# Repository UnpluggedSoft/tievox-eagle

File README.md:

# tievox-eagle
Eagle drawings for TIEVox.

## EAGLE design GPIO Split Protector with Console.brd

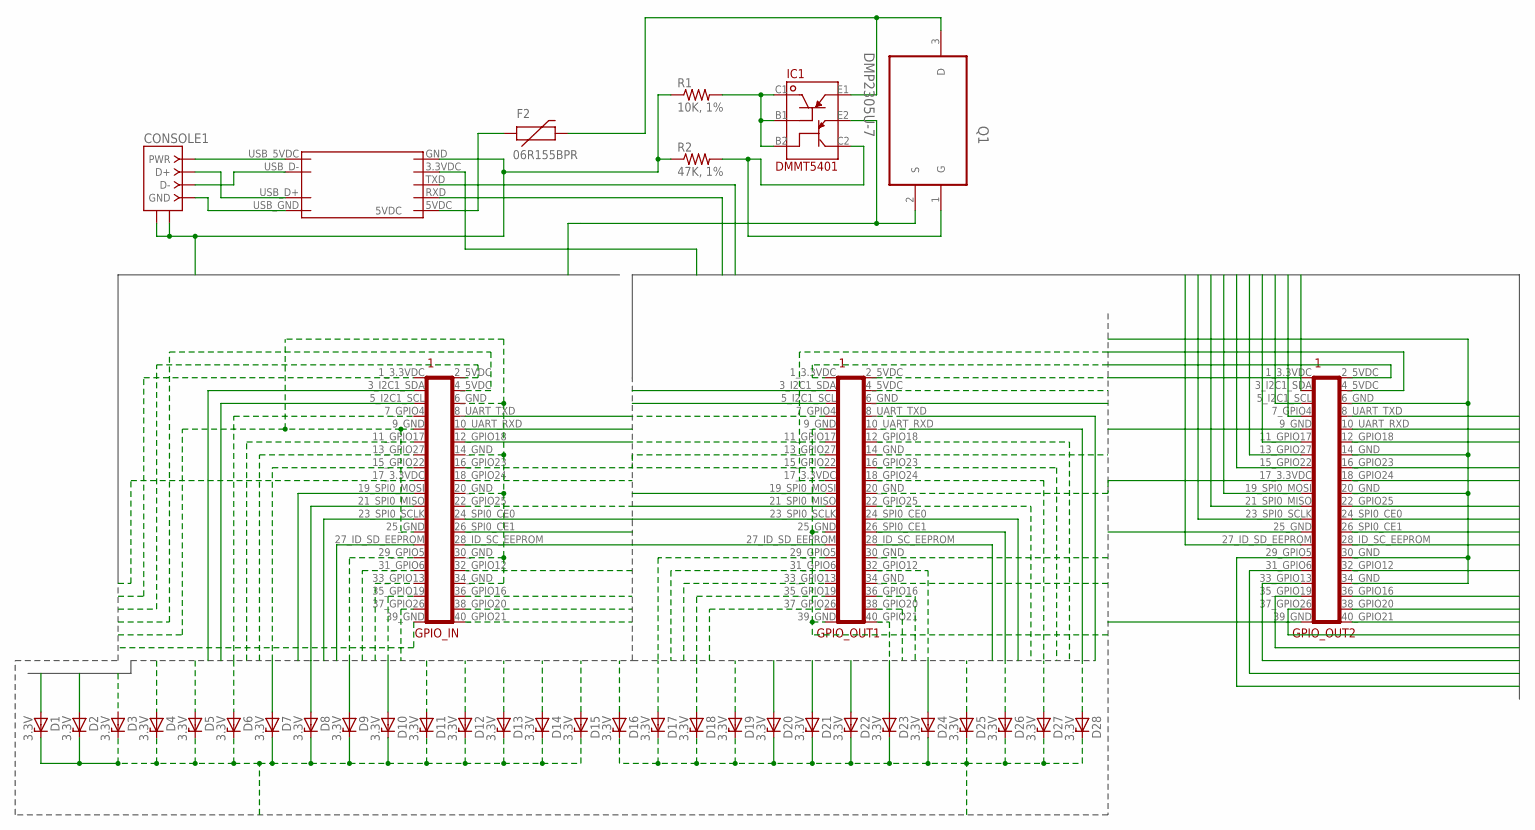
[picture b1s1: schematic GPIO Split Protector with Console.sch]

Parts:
CONSOLE1: USB-RA; USBBF-1
D1, D2, D3, D4, D5, D6, D7, D8, D9, D10, D11, D12, D13, D14, D15, D16, D17, D18, D19, D20, D21, D22, D23, D24, D25, D26, D27, D28: 3.3V; DO41Z10
F2: 06R155BPR; PTC
GPIO_IN: RPI_GPIOUPPER; RPI_GPIO_MALE
GPIO_OUT1, GPIO_OUT2: RPI_GPIOUPPER; RPI_GPIO_MALE
IC1: DMMT5401
Q1: DMP2305U-7; SOT103P240X110-3N
R1: 10K, 1%; 0204/7
R2: 47K, 1%; 0204/7
UART1: GS27159

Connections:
3.3VDC1: GPIO_IN.1_3.3VDC, GPIO_OUT1.1_3.3VDC, GPIO_OUT2.1_3.3VDC
3.3VDC2: GPIO_IN.17_3.3VDC, GPIO_OUT1.17_3.3VDC, GPIO_OUT2.17_3.3VDC
5VDC1: GPIO_IN.2_5VDC, GPIO_OUT1.2_5VDC, GPIO_OUT2.2_5VDC
5VDC2: GPIO_IN.4_5VDC, GPIO_OUT1.4_5VDC, GPIO_OUT2.4_5VDC, IC1.E2, Q1.2 (S)
5VDC_TO_FUSE: F2.P$1 (1), UART1.5VDC
GND: CONSOLE1.CASE1 (SHIELD1), CONSOLE1.CASE2 (SHIELD2), D1.C, D2.C, D3.C, D4.C, D5.C, D6.C, D7.C, D8.C, D9.C, D10.C, D11.C, D12.C, D13.C, D14.C, D15.C, D16.C, D17.C, D18.C, D19.C, D20.C, D21.C, D22.C, D23.C, D24.C, D25.C, D26.C, D27.C, D28.C, GPIO_IN.6_GND, GPIO_IN.9_GND, GPIO_IN.14_GND, GPIO_IN.20_GND, GPIO_IN.25_GND, GPIO_IN.30_GND, GPIO_IN.34_GND, GPIO_IN.39_GND, GPIO_OUT1.6_GND, GPIO_OUT1.9_GND, GPIO_OUT1.14_GND, GPIO_OUT1.20_GND, GPIO_OUT1.25_GND, GPIO_OUT1.30_GND, GPIO_OUT1.34_GND, GPIO_OUT1.39_GND, GPIO_OUT2.6_GND, GPIO_OUT2.9_GND, GPIO_OUT2.14_GND, GPIO_OUT2.20_GND, GPIO_OUT2.25_GND, GPIO_OUT2.30_GND, GPIO_OUT2.34_GND, GPIO_OUT2.39_GND, R1.1, R2.1, UART1.GND
GPIO4: D3.A, GPIO_IN.7_GPIO4, GPIO_OUT1.7_GPIO4, GPIO_OUT2.7_GPIO4
GPIO5: D11.A, GPIO_IN.29_GPIO5, GPIO_OUT1.29_GPIO5, GPIO_OUT2.29_GPIO5
GPIO6: D12.A, GPIO_IN.31_GPIO6, GPIO_OUT1.31_GPIO6, GPIO_OUT2.31_GPIO6
GPIO12: D25.A, GPIO_IN.32_GPIO12, GPIO_OUT1.32_GPIO12, GPIO_OUT2.32_GPIO12
GPIO13: D13.A, GPIO_IN.33_GPIO13, GPIO_OUT1.33_GPIO13, GPIO_OUT2.33_GPIO13
GPIO16: D26.A, GPIO_IN.36_GPIO16, GPIO_OUT1.36_GPIO16, GPIO_OUT2.36_GPIO16, UART1.3.3VDC
GPIO17: D4.A, GPIO_IN.11_GPIO17, GPIO_OUT1.11_GPIO17, GPIO_OUT2.11_GPIO17
GPIO18: D16.A, GPIO_IN.12_GPIO18, GPIO_OUT1.12_GPIO18, GPIO_OUT2.12_GPIO18
GPIO19: D14.A, GPIO_IN.35_GPIO19, GPIO_OUT1.35_GPIO19, GPIO_OUT2.35_GPIO19
GPIO20: D27.A, GPIO_IN.38_GPIO20, GPIO_OUT1.38_GPIO20, GPIO_OUT2.38_GPIO20
GPIO21: D28.A, GPIO_IN.40_GPIO21, GPIO_OUT1.40_GPIO21, GPIO_OUT2.40_GPIO21
GPIO22: D6.A, GPIO_IN.15_GPIO22, GPIO_OUT1.15_GPIO22, GPIO_OUT2.15_GPIO22
GPIO23: D17.A, GPIO_IN.16_GPIO23, GPIO_OUT1.16_GPIO23, GPIO_OUT2.16_GPIO23
GPIO24: D18.A, GPIO_IN.18_GPIO24, GPIO_OUT1.18_GPIO24, GPIO_OUT2.18_GPIO24
GPIO25: D19.A, GPIO_IN.22_GPIO25, GPIO_OUT1.22_GPIO25, GPIO_OUT2.22_GPIO25
GPIO26: D15.A, GPIO_IN.37_GPIO26, GPIO_OUT1.37_GPIO26, GPIO_OUT2.37_GPIO26
GPIO27: D5.A, GPIO_IN.13_GPIO27, GPIO_OUT1.13_GPIO27, GPIO_OUT2.13_GPIO27
I2C_SCL: D2.A, GPIO_IN.5_I2C1_SCL, GPIO_OUT1.5_I2C1_SCL, GPIO_OUT2.5_I2C1_SCL
I2C_SDA: D1.A, GPIO_IN.3_I2C1_SDA, GPIO_OUT1.3_I2C1_SDA, GPIO_OUT2.3_I2C1_SDA
ID_SC: D24.A, GPIO_IN.28_ID_SC_EEPROM, GPIO_OUT1.28_ID_SC_EEPROM, GPIO_OUT2.28_ID_SC_EEPROM
ID_SD: D10.A, GPIO_IN.27_ID_SD_EEPROM (27_ID_SC_EEPROM), GPIO_OUT1.27_ID_SD_EEPROM (27_ID_SC_EEPROM), GPIO_OUT2.27_ID_SD_EEPROM (27_ID_SC_EEPROM)
IN: F2.P$2 (2), IC1.E1, Q1.3 (D)
unnamed: IC1.B1, IC1.B2, IC1.C1, R1.2
unnamed: IC1.C2, Q1.1 (G), R2.2
unnamed: CONSOLE1.4 (GND), UART1.USB_GND
unnamed: CONSOLE1.1 (PWR), UART1.USB_5VDC
unnamed: CONSOLE1.2 (D-), UART1.USB_D-
unnamed: CONSOLE1.3 (D+), UART1.USB_D+
SPI_CE0: D22.A, GPIO_IN.24_SPI0_CE0, GPIO_OUT1.24_SPI0_CE0, GPIO_OUT2.24_SPI0_CE0
SPI_CE1: D23.A, GPIO_IN.26_SPI0_CE1, GPIO_OUT1.26_SPI0_CE1, GPIO_OUT2.26_SPI0_CE1
SPI_MISO: D8.A, GPIO_IN.21_SPI0_MISO, GPIO_OUT1.21_SPI0_MISO, GPIO_OUT2.21_SPI0_MISO
SPI_MOSI: D7.A, GPIO_IN.19_SPI0_MOSI, GPIO_OUT1.19_SPI0_MOSI, GPIO_OUT2.19_SPI0_MOSI
SPI_SCLK: D9.A, GPIO_IN.23_SPI0_SCLK, GPIO_OUT1.23_SPI0_SCLK, GPIO_OUT2.23_SPI0_SCLK
UART_RXD: D21.A, GPIO_IN.10_UART_RXD (10_UART0_RXD), GPIO_OUT1.10_UART_RXD (10_UART0_RXD), GPIO_OUT2.10_UART_RXD (10_UART0_RXD), UART1.RXD
UART_TXD: D20.A, GPIO_IN.8_UART_TXD (8_UART0_TXD), GPIO_OUT1.8_UART_TXD (8_UART0_TXD), GPIO_OUT2.8_UART_TXD (8_UART0_TXD), UART1.TXD

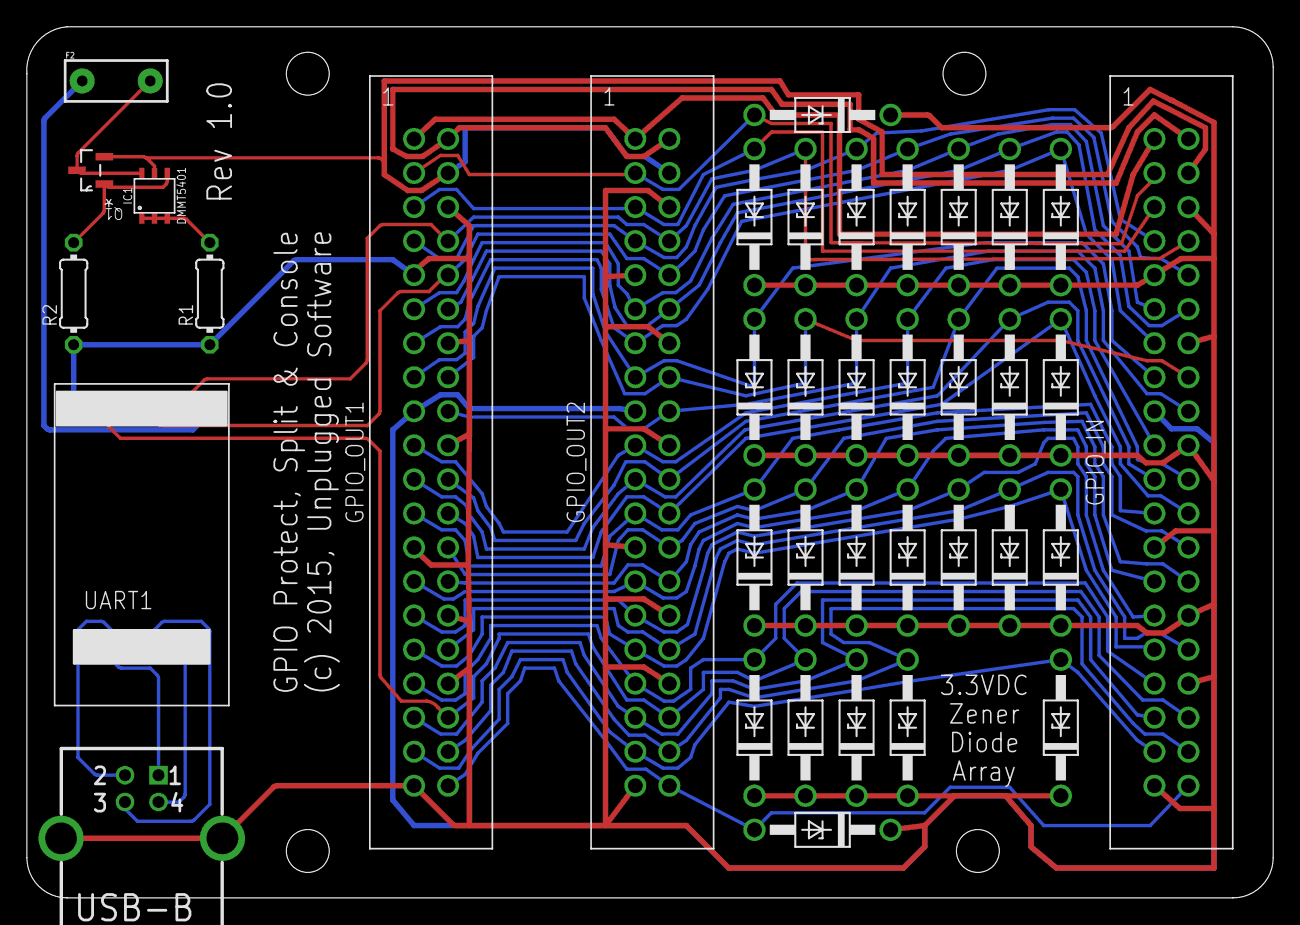
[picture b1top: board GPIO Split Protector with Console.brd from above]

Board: 2 copper layers, 92.9 x 64.9 mm, 38 parts (0 on the bottom side), 41 nets.

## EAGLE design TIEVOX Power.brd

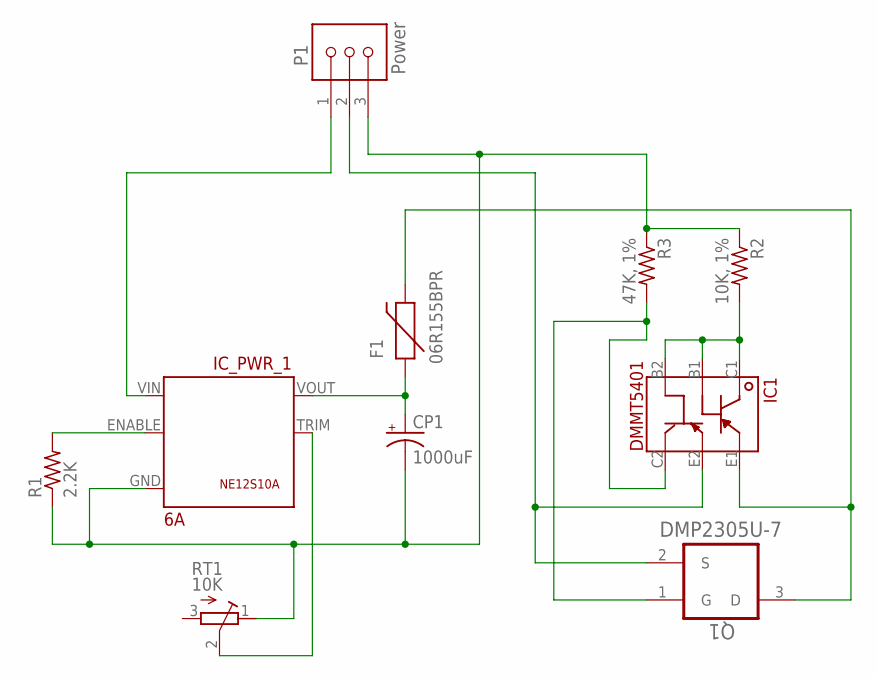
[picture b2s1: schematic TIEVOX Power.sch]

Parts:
CP1: 1000uF; E3,5-8
F1: 06R155BPR; PTC
IC1: DMMT5401
IC_PWR_1: 6A; NE12S
P1: Power; PINHEAD-LOCK-3
Q1: DMP2305U-7; SOT103P240X110-3N
R1: 2.2K; 0207/10
R2: 10K, 1%; 0207/7
R3: 47K, 1%; 0207/7
RT1: 10K; RTRIM3006P

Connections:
+5VDC: IC1.E2, P1.2, Q1.2 (S)
GND: IC1.C2, Q1.1 (G), R3.2
GND_PC: CP1.-, IC_PWR_1.GND, P1.3, R1.1, R2.1, R3.1, RT1.1 (E)
IN: F1.P$2 (2), IC1.E1, Q1.3 (D)
unnamed: IC_PWR_1.VIN, P1.1
unnamed: CP1.+, F1.P$1 (1), IC_PWR_1.VOUT
unnamed: IC_PWR_1.ENABLE, R1.2
unnamed: IC1.B1, IC1.B2, IC1.C1, R2.2
PWR12_TRIM: IC_PWR_1.TRIM, RT1.2 (S)

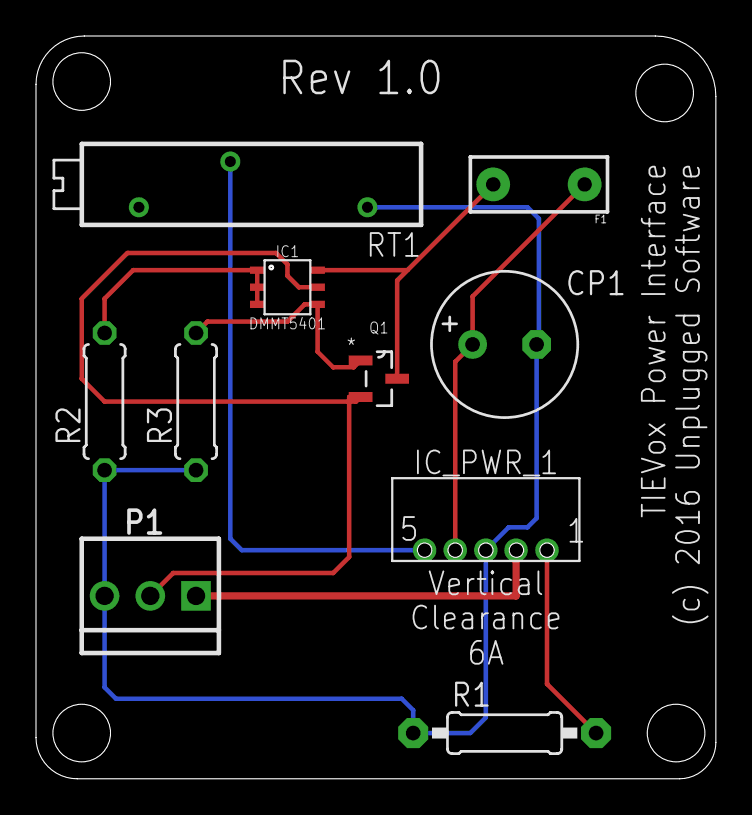
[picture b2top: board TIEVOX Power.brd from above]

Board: 2 copper layers, 37.6 x 41.1 mm, 10 parts (0 on the bottom side), 9 nets.

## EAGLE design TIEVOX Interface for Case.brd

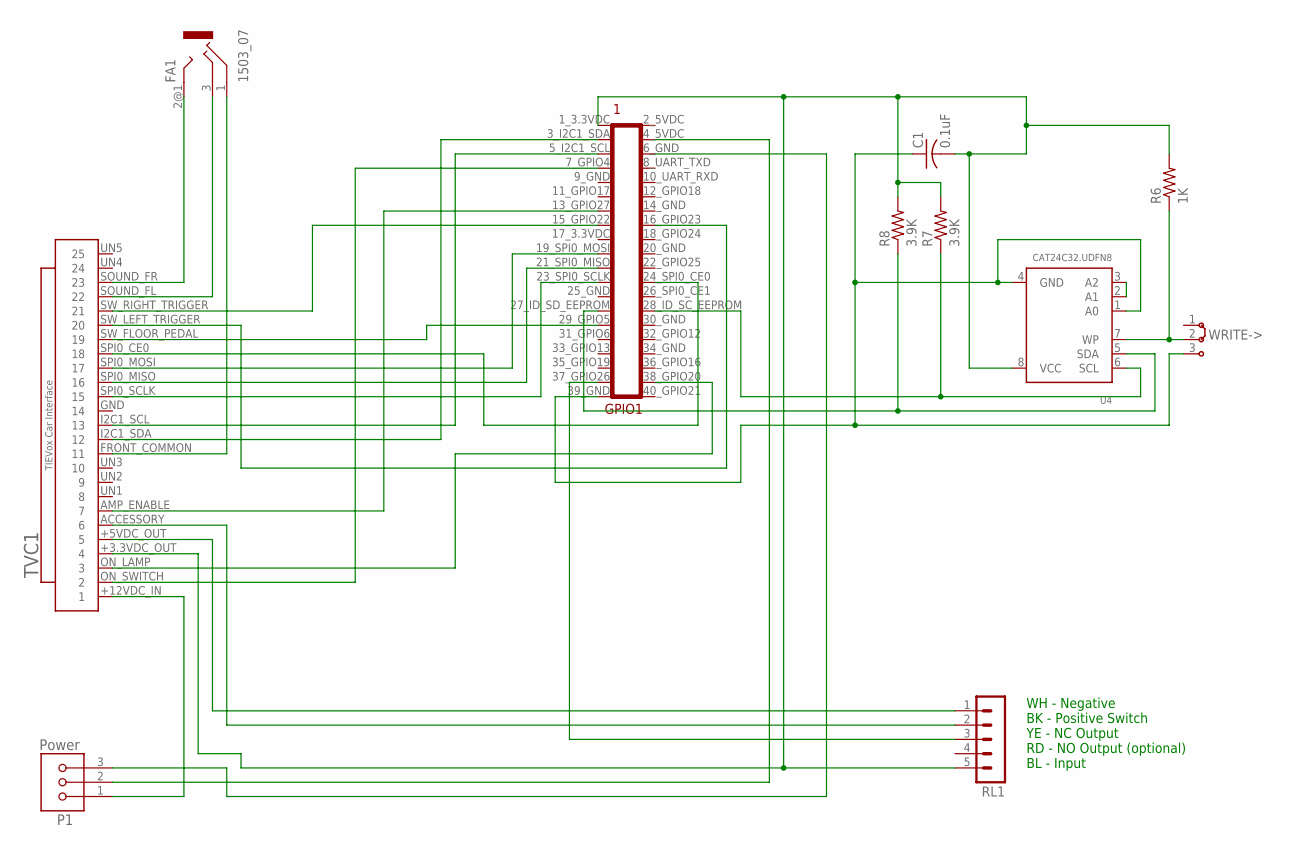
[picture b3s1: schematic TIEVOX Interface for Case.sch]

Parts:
C1: 0.1uF; C025-050X050
FA1: 1503_07
GPIO1: RPI_GPIO_MALE_SHROUD; RPI_GPIO_MALE
P1: Power; PINHEAD-LOCK-3
R6: 1K; 0207/10
R7, R8: 3.9K; 0207/10
RL1: MA05-1
TVC1: TIEVox Car Interface; D-SUB25
U4: CAT24C32.UDFN8; SOIC8_150MIL
WRITE->: J2X2MM; 04C

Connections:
2_5VDC: GPIO1.2_5VDC
9_GND: GPIO1.9_GND
14_GND: GPIO1.14_GND
17_3.3VDC: GPIO1.17_3.3VDC
20_GND: GPIO1.20_GND
25_GND: GPIO1.25_GND
30_GND: GPIO1.30_GND
34_GND: GPIO1.34_GND
+3.3VDC: C1.2, GPIO1.1_3.3VDC, R6.2, R7.2, R8.2, RL1.5, TVC1.+3.3VDC_OUT (4), U4.8 (VCC)
+5VDC: GPIO1.4_5VDC, P1.2, TVC1.+5VDC_OUT (5)
GND: GPIO1.6_GND, P1.3, RL1.1
GND_39: C1.1, GPIO1.39_GND, U4.1 (A0), U4.4 (GND), WRITE->.3
unnamed: U4.2 (A1), U4.3 (A2)
unnamed: GPIO1.28_ID_SC_EEPROM, R7.1, U4.6 (SCL)
unnamed: GPIO1.27_ID_SD_EEPROM (27_ID_SC_EEPROM), R8.1, U4.5 (SDA)
unnamed: FA1.1, TVC1.FRONT_COMMON (11)
unnamed: GPIO1.23_SPI0_SCLK, TVC1.SPI0_SCLK (15)
unnamed: GPIO1.21_SPI0_MISO, TVC1.SPI0_MISO (16)
unnamed: GPIO1.19_SPI0_MOSI, TVC1.SPI0_MOSI (17)
unnamed: FA1.2@1 (2), TVC1.SOUND_FR (23)
unnamed: FA1.3, TVC1.SOUND_FL (22)
unnamed: GPIO1.5_I2C1_SCL, TVC1.I2C1_SCL (13)
unnamed: GPIO1.3_I2C1_SDA, TVC1.I2C1_SDA (12)
unnamed: GPIO1.24_SPI0_CE0, TVC1.SPI0_CE0 (18)
unnamed: RL1.2, TVC1.ACCESSORY (6)
unnamed: GPIO1.13_GPIO27, TVC1.AMP_ENABLE (7)
unnamed: GPIO1.7_GPIO4, TVC1.ON_SWITCH (2)
unnamed: GPIO1.38_GPIO20, TVC1.ON_LAMP (3)
unnamed: GPIO1.29_GPIO5, TVC1.SW_FLOOR_PEDAL (19)
unnamed: GPIO1.15_GPIO22, TVC1.SW_RIGHT_TRIGGER (21)
unnamed: GPIO1.16_GPIO23, TVC1.SW_LEFT_TRIGGER (20)
unnamed: GPIO1.37_GPIO26, RL1.3
unnamed: R6.1, U4.7 (WP), WRITE->.2
PWR12_IN: P1.1, TVC1.+12VDC_IN (1)

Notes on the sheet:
WH - Negative BK - Positive Switch YE - NC Output RD - NO Output (optional) BL - Input

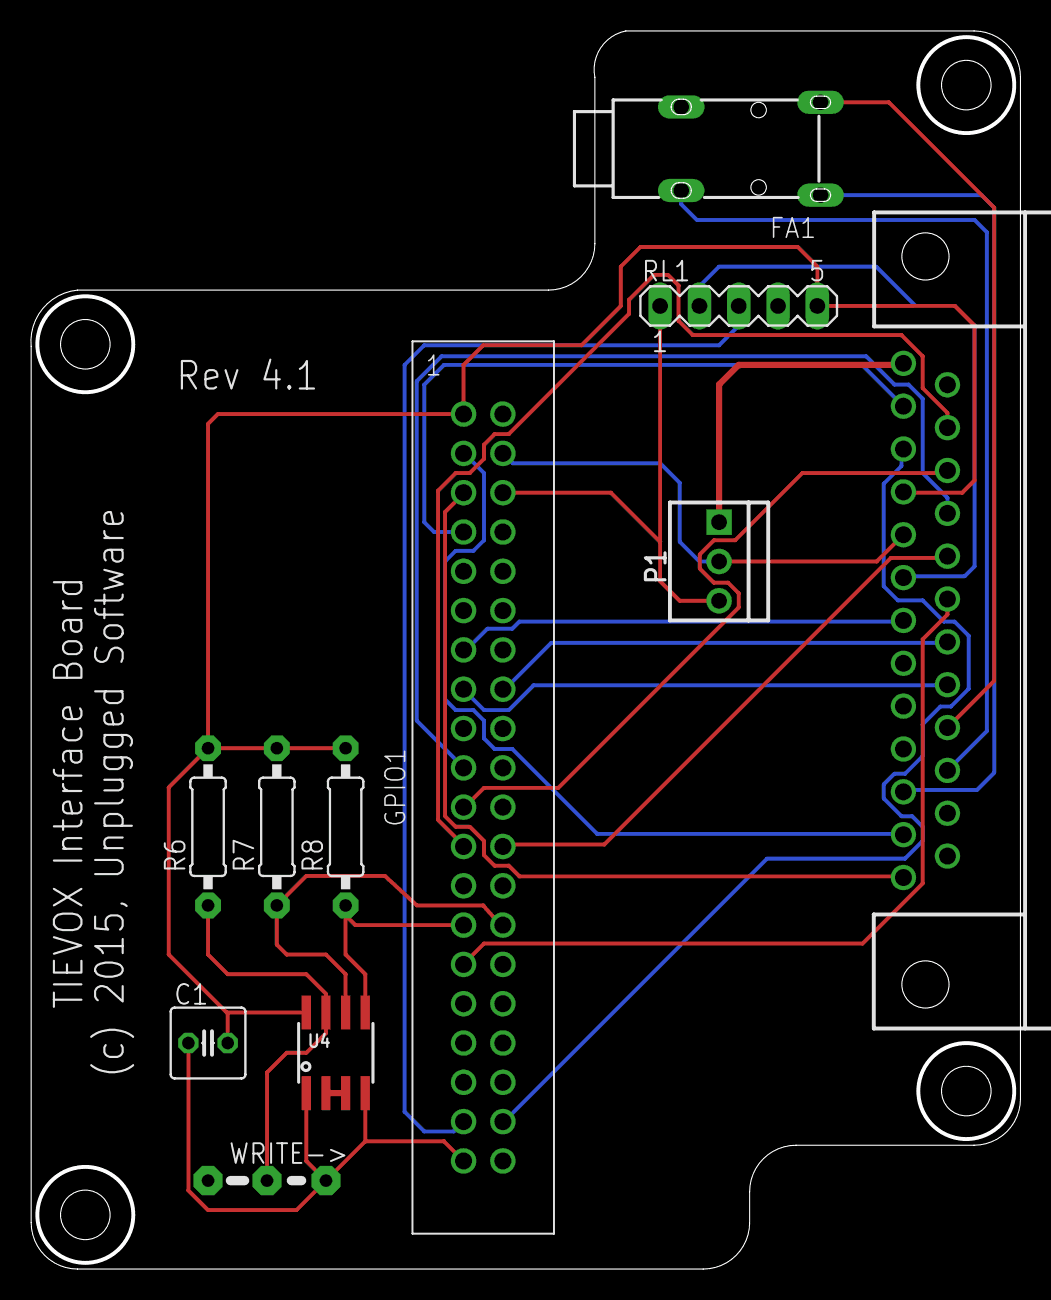
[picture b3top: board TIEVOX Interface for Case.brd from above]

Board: 2 copper layers, 63.7 x 79.7 mm, 11 parts (0 on the bottom side), 26 nets.

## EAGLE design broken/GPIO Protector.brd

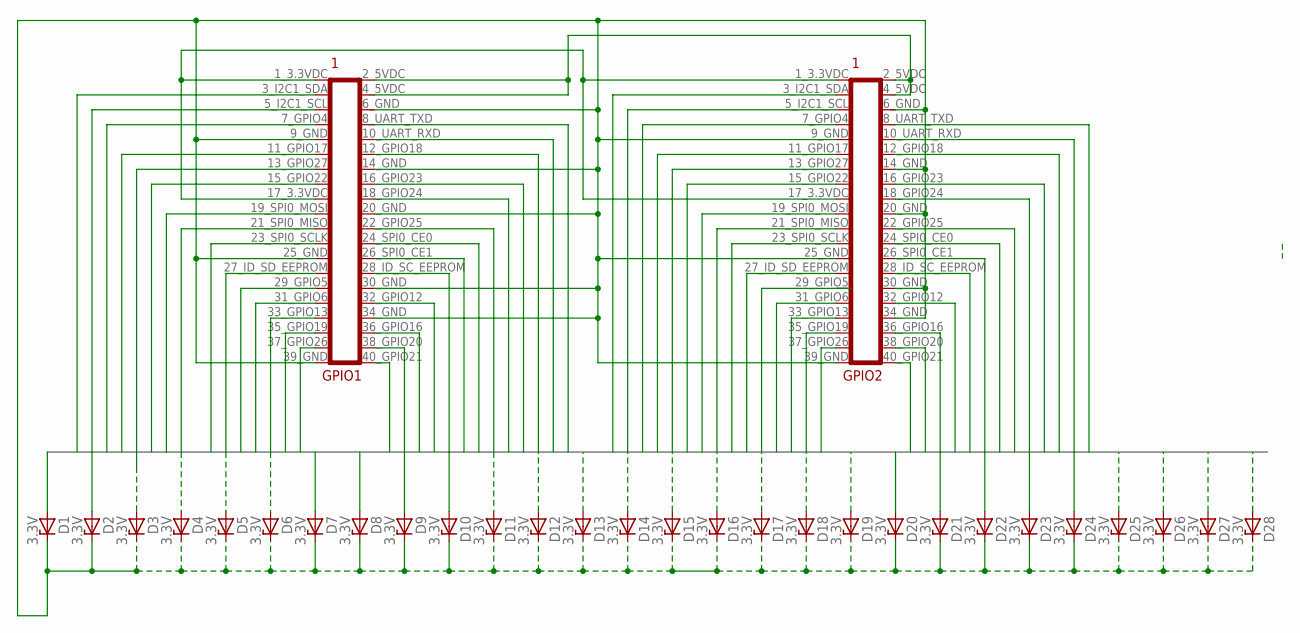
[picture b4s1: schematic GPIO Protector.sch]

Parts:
D1, D2, D3, D4, D5, D6, D7, D8, D9, D10, D11, D12, D13, D14, D15, D16, D17, D18, D19, D20, D21, D22, D23, D24, D25, D26, D27, D28: 3.3V; DO41Z10
GPIO1, GPIO2: RPI_GPIOUPPER; RPI_GPIO_MALE

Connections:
3.3VDC: GPIO1.1_3.3VDC, GPIO1.17_3.3VDC, GPIO2.1_3.3VDC, GPIO2.17_3.3VDC
5VDC: GPIO1.2_5VDC, GPIO1.4_5VDC, GPIO2.2_5VDC, GPIO2.4_5VDC
GND: D1.C, D2.C, D3.C, D4.C, D5.C, D6.C, D7.C, D8.C, D9.C, D10.C, D11.C, D12.C, D13.C, D14.C, D15.C, D16.C, D17.C, D18.C, D19.C, D20.C, D21.C, D22.C, D23.C, D24.C, D25.C, D26.C, D27.C, D28.C, GPIO1.6_GND, GPIO1.9_GND, GPIO1.14_GND, GPIO1.20_GND, GPIO1.25_GND, GPIO1.30_GND, GPIO1.34_GND, GPIO1.39_GND, GPIO2.6_GND, GPIO2.9_GND, GPIO2.14_GND, GPIO2.20_GND, GPIO2.25_GND, GPIO2.30_GND, GPIO2.34_GND, GPIO2.39_GND
GPIO4: D3.A, GPIO1.7_GPIO4, GPIO2.7_GPIO4
GPIO5: D11.A, GPIO1.29_GPIO5
GPIO6: D12.A, GPIO1.31_GPIO6, GPIO2.31_GPIO6
GPIO12: D25.A, GPIO1.32_GPIO12, GPIO2.32_GPIO12
GPIO13: D13.A, GPIO1.33_GPIO13, GPIO2.33_GPIO13
GPIO16: D26.A, GPIO1.36_GPIO16, GPIO2.36_GPIO16
GPIO17: D4.A, GPIO1.11_GPIO17, GPIO2.11_GPIO17
GPIO18: D16.A, GPIO1.12_GPIO18, GPIO2.12_GPIO18
GPIO19: D14.A, GPIO1.35_GPIO19, GPIO2.35_GPIO19
GPIO20: D27.A, GPIO1.38_GPIO20, GPIO2.38_GPIO20
GPIO21: D28.A, GPIO1.40_GPIO21, GPIO2.40_GPIO21
GPIO22: D6.A, GPIO1.15_GPIO22, GPIO2.15_GPIO22
GPIO23: D17.A, GPIO1.16_GPIO23, GPIO2.16_GPIO23
GPIO24: D18.A, GPIO1.18_GPIO24, GPIO2.18_GPIO24
GPIO25: D19.A, GPIO1.22_GPIO25, GPIO2.22_GPIO25
GPIO26: D15.A, GPIO1.37_GPIO26, GPIO2.37_GPIO26
GPIO27: D5.A, GPIO1.13_GPIO27, GPIO2.13_GPIO27
I2C_SCL: D2.A, GPIO1.5_I2C1_SCL, GPIO2.5_I2C1_SCL
I2C_SDA: D1.A, GPIO1.3_I2C1_SDA, GPIO2.3_I2C1_SDA
ID_SC: D24.A, GPIO1.28_ID_SC_EEPROM, GPIO2.28_ID_SC_EEPROM
ID_SD: D10.A, GPIO1.27_ID_SD_EEPROM (27_ID_SC_EEPROM), GPIO2.27_ID_SD_EEPROM (27_ID_SC_EEPROM)
SPI_CE0: D22.A, GPIO1.24_SPI0_CE0, GPIO2.24_SPI0_CE0
SPI_CE1: D23.A, GPIO1.26_SPI0_CE1, GPIO2.26_SPI0_CE1
SPI_MISO: D8.A, GPIO1.21_SPI0_MISO, GPIO2.21_SPI0_MISO
SPI_MOSI: D7.A, GPIO1.19_SPI0_MOSI, GPIO2.19_SPI0_MOSI
SPI_SCLK: D9.A, GPIO1.23_SPI0_SCLK, GPIO2.23_SPI0_SCLK
UART_RXD: D21.A, GPIO1.10_UART_RXD (10_UART0_RXD), GPIO2.10_UART_RXD (10_UART0_RXD)
UART_TXD: D20.A, GPIO1.8_UART_TXD (8_UART0_TXD), GPIO2.8_UART_TXD (8_UART0_TXD)

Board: 2 copper layers, 30 parts (0 on the bottom side), 31 nets, no tracks yet.

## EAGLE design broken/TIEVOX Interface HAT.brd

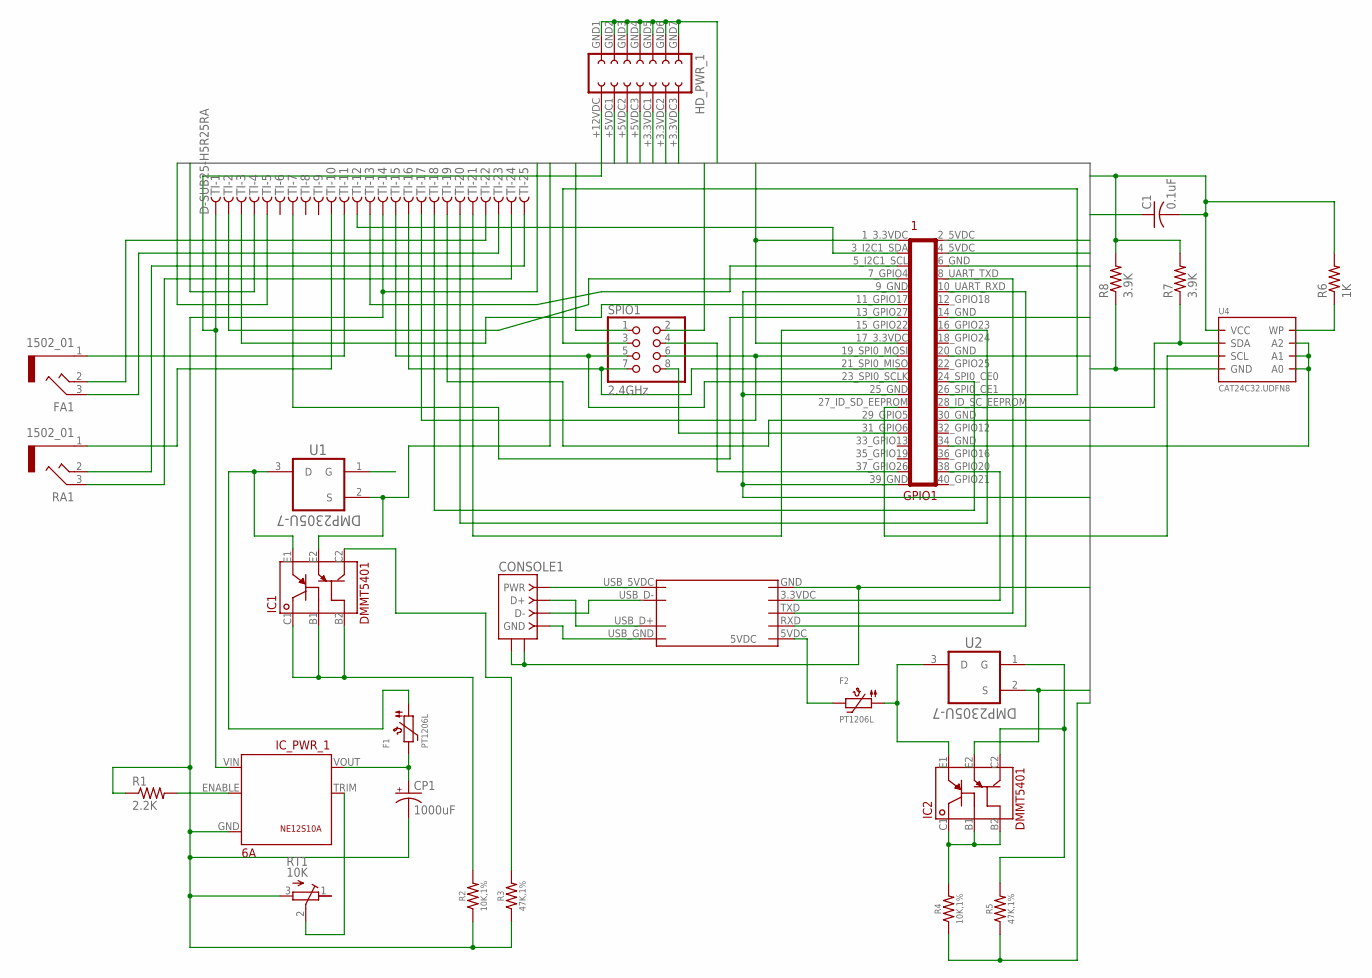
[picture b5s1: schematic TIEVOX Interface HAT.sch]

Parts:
C1: 0.1uF; C1005
CONSOLE1: USB-RA; USBBF-1
CP1: 1000uF; E3,5-8
F1, F2: PT1206L; 1206
FA1: 1502_01
GPIO1: RPI_GPIOUPPER; RPI_GPIO_MALE
HD_PWR_1: PWR_HDR_FEMALE_2X7
IC1, IC2: DMMT5401
IC_PWR_1: 6A; NE12S
R1: 2.2K; 0207/10
R2, R4: 10K,1%; R01005
R3, R5: 47K,1%; R01005
R6: 1K; R1005
R7, R8: 3.9K; R1005
RA1: 1502_01
RT1: 10K; RTRIM3006P
SPIO1: 2.4GHz; 2X04
TI: D-SUB25-H5R25RA; H5R25RA
U1, U2: DMP2305U-7; SOT103P240X110-3N
U4: CAT24C32.UDFN8; UDFN8
UART1: GS27159

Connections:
5VDC: F2.2, UART1.5VDC
+3.3VDC: C1.2, GPIO1.1_3.3VDC, GPIO1.17_3.3VDC, HD_PWR_1.+3.3VDC1 (10), HD_PWR_1.+3.3VDC2 (12), HD_PWR_1.+3.3VDC3 (14), R6.2, R7.2, R8.2, SPIO1.2, TI.4, U4.8 (VCC)
+5VDC: GPIO1.2_5VDC, GPIO1.4_5VDC, HD_PWR_1.+5VDC1 (4), HD_PWR_1.+5VDC2 (6), HD_PWR_1.+5VDC3 (8), IC1.E2, IC2.E2, TI.5, U1.2 (S), U2.2 (S)
CONSOLE_ON: GPIO1.38_GPIO20, UART1.3.3VDC
GND: C1.1, CONSOLE1.CASE1 (SHIELD1), CONSOLE1.CASE2 (SHIELD2), CP1.-, GPIO1.6_GND, GPIO1.9_GND, GPIO1.14_GND, GPIO1.20_GND, GPIO1.25_GND, GPIO1.30_GND, GPIO1.34_GND, GPIO1.39_GND, HD_PWR_1.GND1 (1), HD_PWR_1.GND2 (3), HD_PWR_1.GND3 (5), HD_PWR_1.GND4 (7), HD_PWR_1.GND5 (9), HD_PWR_1.GND6 (11), HD_PWR_1.GND7 (13), IC_PWR_1.GND, R1.1, R2.1, R3.1, R4.1, R5.1, R8.1, RT1.3 (A), SPIO1.1, TI.14, U4.1 (A0), U4.2 (A1), U4.3 (A2), U4.4 (GND), U4.PAD (GND), UART1.GND
unnamed: GPIO1.19_SPI0_MOSI, SPIO1.6, TI.17
unnamed: GPIO1.21_SPI0_MISO, SPIO1.7, TI.16
unnamed: GPIO1.23_SPI0_SCLK, SPIO1.5, TI.15
unnamed: GPIO1.26_SPI0_CE1, SPIO1.3
unnamed: GPIO1.31_GPIO6, SPIO1.8
unnamed: GPIO1.37_GPIO26, SPIO1.4
unnamed: GPIO1.7_GPIO4, TI.2
unnamed: GPIO1.11_GPIO17, TI.3
unnamed: GPIO1.13_GPIO27, TI.7
unnamed: GPIO1.24_SPI0_CE0, TI.18
unnamed: GPIO1.29_GPIO5, TI.19
unnamed: GPIO1.16_GPIO23, TI.20
unnamed: GPIO1.15_GPIO22, TI.21
unnamed: CONSOLE1.4 (GND), UART1.USB_GND
unnamed: CONSOLE1.1 (PWR), UART1.USB_5VDC
unnamed: CONSOLE1.2 (D-), UART1.USB_D-
unnamed: CONSOLE1.3 (D+), UART1.USB_D+
unnamed: GPIO1.8_UART_TXD (8_UART0_TXD), UART1.TXD
unnamed: GPIO1.10_UART_RXD (10_UART0_RXD), UART1.RXD
unnamed: FA1.1, TI.11
unnamed: RA1.1, TI.10
unnamed: RA1.3 (2), TI.24
unnamed: RA1.2 (3), TI.25
unnamed: FA1.3 (2), TI.23
unnamed: FA1.2 (3), TI.22
unnamed: GPIO1.3_I2C1_SDA, TI.12
unnamed: GPIO1.5_I2C1_SCL, TI.13
unnamed: CP1.+, F1.2, IC_PWR_1.VOUT
unnamed: IC_PWR_1.ENABLE, R1.2
unnamed: F1.1, IC1.E1, U1.3 (D)
unnamed: IC1.B1, IC1.B2, IC1.C1, R2.2
unnamed: F2.1, IC2.E1, U2.3 (D)
unnamed: IC1.C2, R3.2
unnamed: IC2.C2, R5.2, U2.1 (G)
unnamed: IC2.B1, IC2.B2, IC2.C1, R4.2
unnamed: GPIO1.27_ID_SD_EEPROM (27_ID_SC_EEPROM), U4.6 (SCL)
unnamed: R6.1, U4.7 (WP)
unnamed: GPIO1.28_ID_SC_EEPROM, R7.1, U4.5 (SDA)
PWR12_IN: HD_PWR_1.+12VDC (2), IC_PWR_1.VIN, TI.1
PWR12_TRIM: IC_PWR_1.TRIM, RT1.2 (S)

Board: 2 copper layers, 27 parts (0 on the bottom side), 45 nets, no tracks yet.

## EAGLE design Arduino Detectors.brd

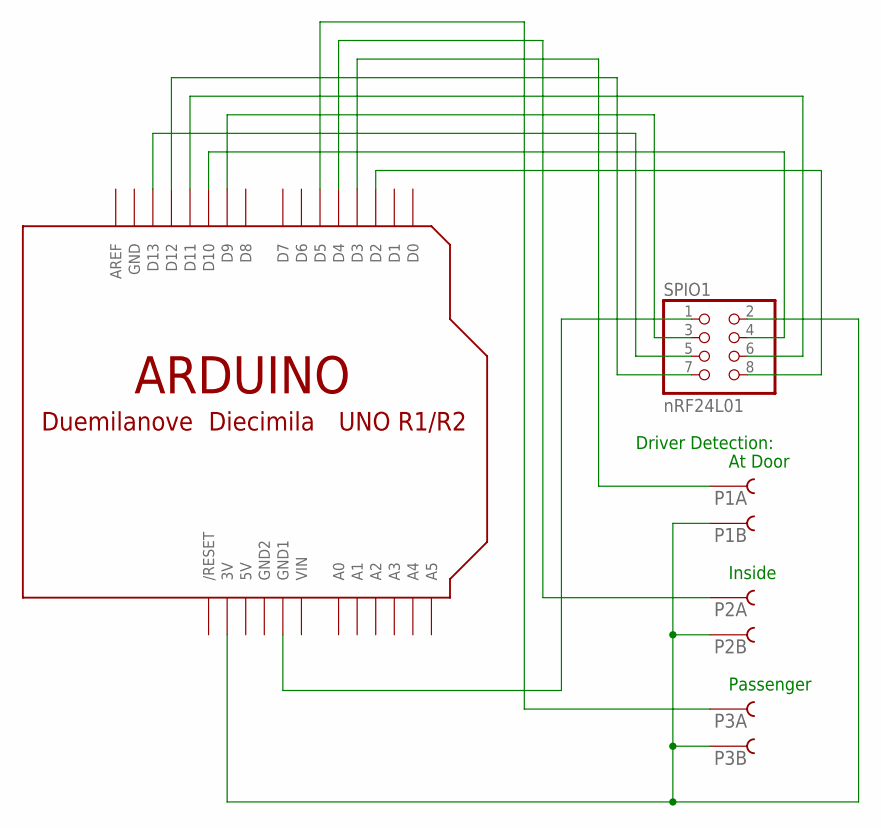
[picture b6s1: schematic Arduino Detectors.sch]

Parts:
P1: ATDOOR; 30.202
P2: INSIDE; 30.202
P3: PASSENGER; 30.202
SPIO1: nRF24L01; 2X04
U$1: ARDUINO-BPLACE

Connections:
5V: U$1.5V
GND: U$1.GND
GND2: U$1.GND2
unnamed: SPIO1.1, U$1.GND1
unnamed: P1.2, P2.2, P3.2, SPIO1.2, U$1.3V
unnamed: SPIO1.3, U$1.D9
unnamed: SPIO1.4, U$1.D10
unnamed: SPIO1.5, U$1.D13
unnamed: SPIO1.6, U$1.D11
unnamed: SPIO1.7, U$1.D12
unnamed: SPIO1.8, U$1.D2
unnamed: P1.1, U$1.D3
unnamed: P2.1, U$1.D4
unnamed: P3.1, U$1.D5
VIN: U$1.VIN

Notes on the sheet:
Driver Detection:
At Door
Inside
Passenger

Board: 2 copper layers, 5 parts (0 on the bottom side), 11 nets, no tracks yet.

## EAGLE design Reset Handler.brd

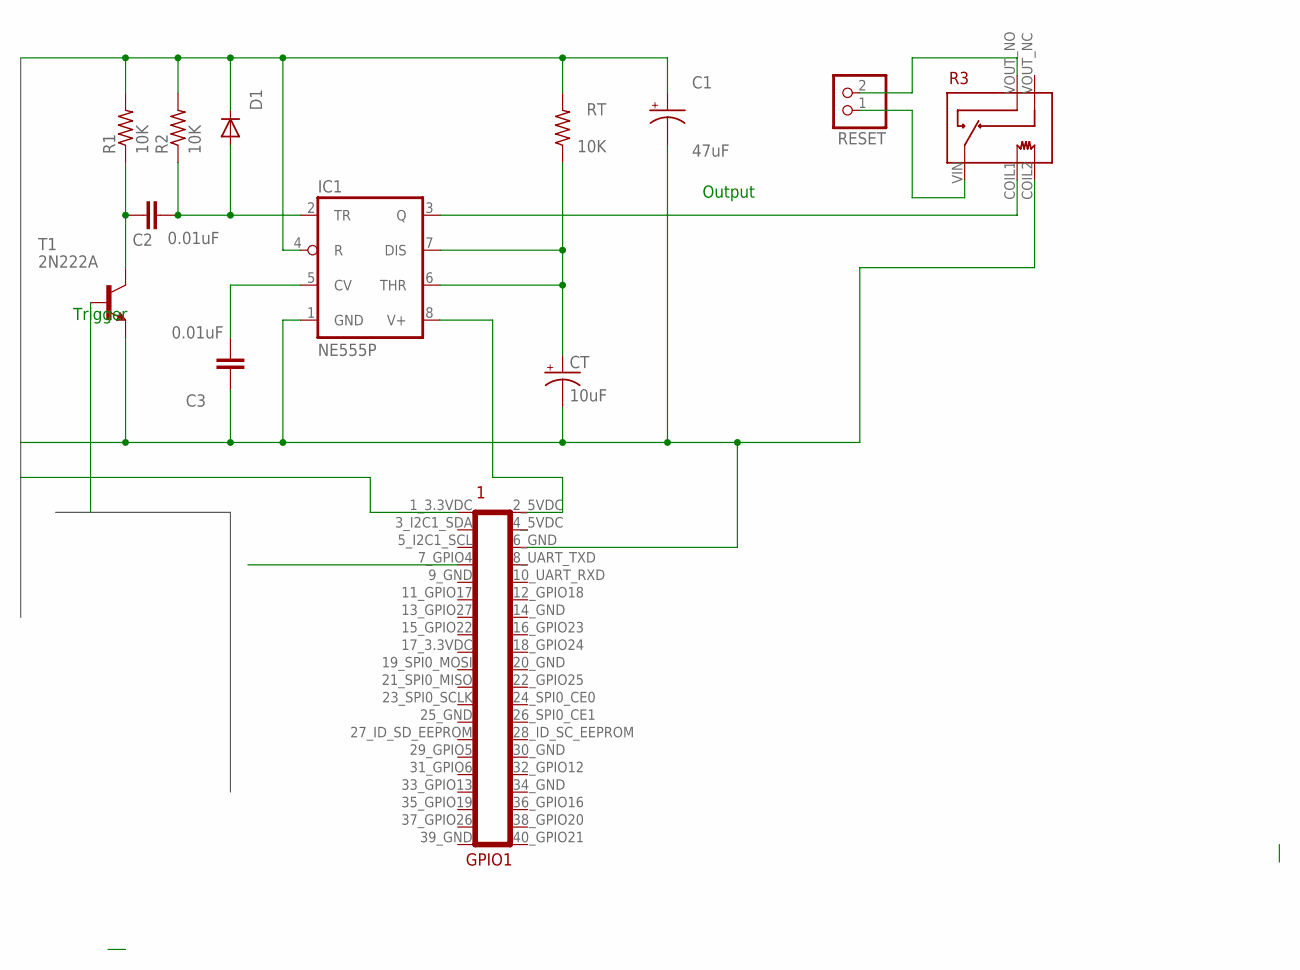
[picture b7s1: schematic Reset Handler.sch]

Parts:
C1: 47uF; E2,5-5
C2, C3: 0.01uF; C10B4
CT: 10uF; E2,5-5
D1: 1N4148; DO35-7
GPIO1: RPI_GPIO_MALE_OPEN; RPI_GPIO_FEMALE_TOP
IC1: NE555P; DIL08
R1, R2: 10K; 0207/10
R3: 5VDC; OUAZ-SS1*
RESET: PINHD-1X2; 1X02
RT: 10K; 0207/10
T1: 2N222A; TO92-EBC

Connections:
4_5VDC: GPIO1.4_5VDC
9_GND: GPIO1.9_GND
14_GND: GPIO1.14_GND
17_3.3VDC: GPIO1.17_3.3VDC
20_GND: GPIO1.20_GND
25_GND: GPIO1.25_GND
30_GND: GPIO1.30_GND
34_GND: GPIO1.34_GND
39_GND: GPIO1.39_GND
+3.3VDC: C1.+, D1.C, GPIO1.1_3.3VDC, IC1.4 (R), R1.2, R2.2, RT.2
GND: C1.-, C3.1, CT.-, GPIO1.6_GND, IC1.1 (GND), R3.COIL2, T1.E
GPIO_4: GPIO1.7_GPIO4, T1.B
unnamed: C2.2, R1.1, T1.C
unnamed: C2.1, D1.A, IC1.2 (TR), R2.1
unnamed: CT.+, IC1.6 (THR), IC1.7 (DIS), RT.1
unnamed: GPIO1.2_5VDC, IC1.8 (V+)
unnamed: C3.2, IC1.5 (CV)
unnamed: R3.VIN, RESET.1
unnamed: R3.VOUT_NO, RESET.2
RESET_OUT: IC1.3 (Q), R3.COIL1

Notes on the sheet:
Output
Trigger

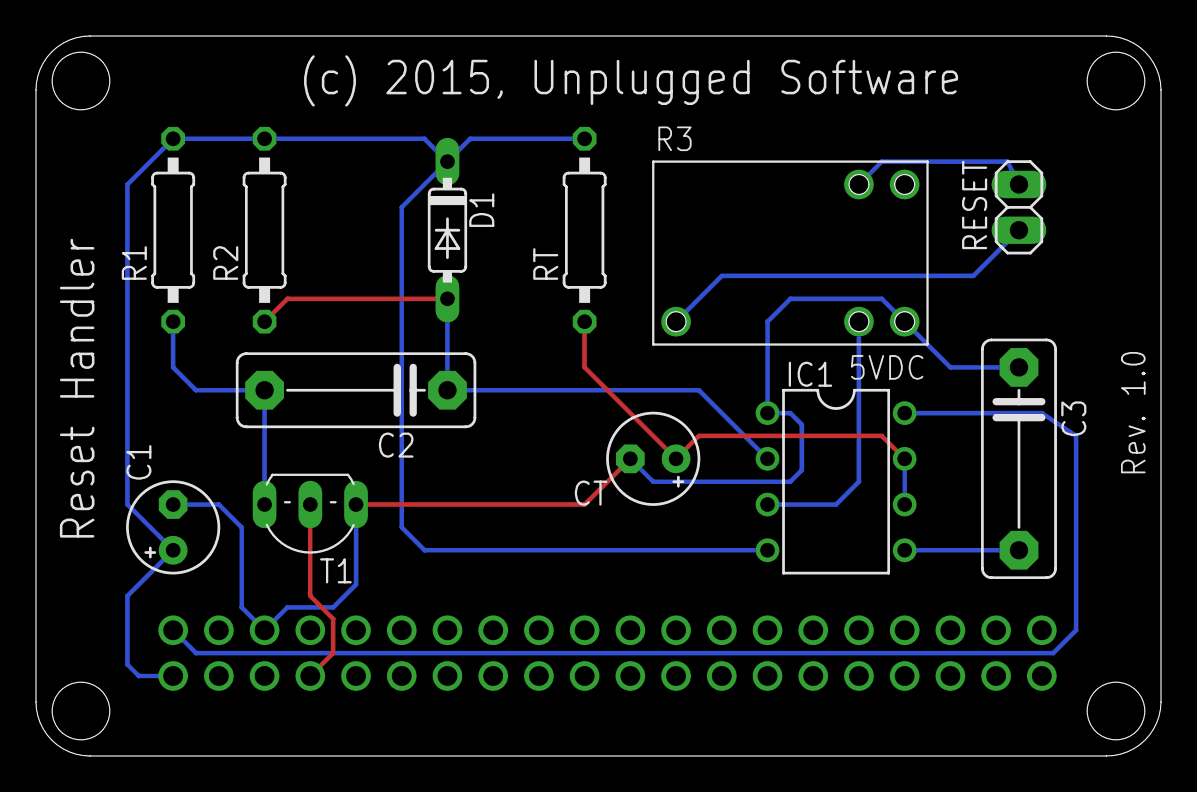
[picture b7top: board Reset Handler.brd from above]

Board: 2 copper layers, 62.5 x 40.0 mm, 13 parts (0 on the bottom side), 11 nets.

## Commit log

2015-09-22 Added current projects as of 9/21/2015.
2015-09-22 Added basic README.
2015-09-23 Split TIEVOX Interface into two separate boards, a HAT and a version for the case I will be using that does not satisfy all the HAT requirements.
2015-09-23 Added LICENSE.md.
    Exported library for GPIO Protect & Split.
2015-09-24 Removed power header. Not sure that it's needed, and need to see if that'll help get everything routed.
2015-09-24 Removed extraneous ground and +VDC connections to GPIO to aid in routing.
2015-10-02 Finished Reset Handler board.
2015-10-02 Another attempt to build Interface without vias.
2015-10-04 Moved some things to broken for now. May fix them later.
    Added console to split protector in GPIO Split Protector with Console.
    Added Arduino Detectors shield.
2015-10-05 Updated TIEVOX Interface for Case:
    - Removed console circuit
    - Replaced audio jacks to use ones purchased
    - Remapped circuit schematic
    - Added backpower protection back in
    - Still needs traces drawn.
2015-10-19 Added printables for split/protect circuit for fab of board.
    Added Accessory Relay header to interface board.
2016-05-17 Should have working versions of all required boards now.
    Updated to No Commercial license.

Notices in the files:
GPIO Split Protector with Console.brd:
(c) 2015, Unplugged Software
TIEVOX Power.brd:
(c) 2016 Unplugged Software
parts and their libraries:
SparkFun-PowerIC: Licensing: CC v3.0 Share-Alike You are welcome to use this library for commercial purposes.
microbuilder: This work is placed in the public domain, and may be freely used for commercial and non-commercial work with the following conditions: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
